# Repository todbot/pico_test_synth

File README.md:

# pico_test_synth

A simple 
[Raspberry Pi Pico RP2040 or Pico 2 RP2350](https://www.raspberrypi.com/documentation/microcontrollers/raspberry-pi-pico.html)-based
synth to experiment with [`synthio`](https://github.com/todbot/circuitpython-synthio-tricks) and [Mozzi](https://github.com/sensorium/Mozzi).

### pico_test_synth2

### pico_test_synth, the original

<h3>video demo</h3>

** **[Available on Tindie](https://www.tindie.com/products/todbot/pico_test_synth/)** **

### Features

* [PCM5102 I2S DAC](https://todbot.com/blog/2023/05/16/cheap-stereo-line-out-i2s-dac-for-circuitpython-arduino-synths/) footprint for high-quality stereo audio out
* Optoisolated MIDI Input via [MIDI TRS-A 3.5mm jack](https://www.perfectcircuit.com/make-noise-0-coast-midi-cable.html)
* MIDI output via MIDI TRS-A 3.5mm jack
* Two pots for controlling parameters
* One switch for controlling parameters
* 16 capsense touch buttons for synth triggering
* USB MIDI in/out of course too
* **(NOTE: the pico_test_synth1 PCB will NOT work with the Pico2, since its RP2350 chip has a hardware error)**

#### pico_test_synth2 vs pico_test_synth

- Both use the same components
- Both run the same code 
- Both fit in the same enclosure
- `pico_test_synth2` drawn in Kicad; `pico_test_synth` drawn in Eagle
- `pico_test_synth2` has square buttons; `pico_test_synth` has round buttons
- `pico_test_synth2` can work with Pico 2 and Pico 
- `pico_test_synth` can only work with Pico1

### Software

Programs written for [`qtpy_synth`](https://github.com/todbot/qtpy_synth/)
will work with this board too with minimal changes.

Some programs written specifically for this board:

* [TBish](https://github.com/todbot/pico_test_synth/tree/main/circuitpython/tbish/) - a TB303-like synth demo ([video demo](https://www.youtube.com/watch?v=1AflpXbEIno))
* [monosynth1](https://github.com/todbot/pico_test_synth/tree/main/arduino/monosynth1) - a full Moog-like monosynth written in Arduino & Mozzi 
* [hwtest](https://github.com/todbot/pico_test_synth/tree/main/circuitpython/hwtest/code.py) - test out the hardware with a simple synth ([video demo](https://www.youtube.com/watch?v=9U2Dn7ckdbs))
* [wavesynth](https://github.com/todbot/pico_test_synth/tree/main/circuitpython/wavesynth/) - port of wavesynth for qtpy_synth board with some improvements

#### See also:
- [CircuitPython Synthio Tricks](https://github.com/todbot/circuitpython-synthio-tricks)
  - Contains [many other synthio examples](https://github.com/todbot/circuitpython-synthio-tricks/tree/main/examples) that can work with this synth with minimal changes
- [Synthio Tutorial](https://todbot.github.io/CircuitPython_Synthio_Tutorial/) 
  - a getting-started guide for `synthio` ending with some full synthesiser voices 

### Enclosure

As seen in the photos, there is a simple [3d-printable enclosure available on Printables](https://www.printables.com/model/784414-case-for-pico_test_synth-circuitpython-synthesizer). 
It's fast to print and you can snap the PCB in to quickly get started,
or use M2.5 screws and nuts to secure the PCB more permanently.

### Pins used

The board uses all of the Raspberry Pi Pico pins:

* `board.GP28` - middle button
* `board.GP27` - right knob
* `board.GP26` - left knob
* `board.GP22` - I2S data
* `board.GP21` - I2S LR  clock
* `board.GP20` - I2S bit clock
* `board.GP19` - I2C SCL for OLED display
* `board.GP18` - I2C SDA for OLED display
* `board.GP17` - TRS UART MIDI in
* `board.GP16` - TRS UART MIDI out
* `board.GP15`..`board.GP0` -- touch pads 1-16

For more details see [`hwtest/code.py`](https://github.com/todbot/pico_test_synth/tree/main/circuitpython/hwtest/code.py).

### Schematics

#### pico_test_synth2 ####

#### pico_test_synth, original ####

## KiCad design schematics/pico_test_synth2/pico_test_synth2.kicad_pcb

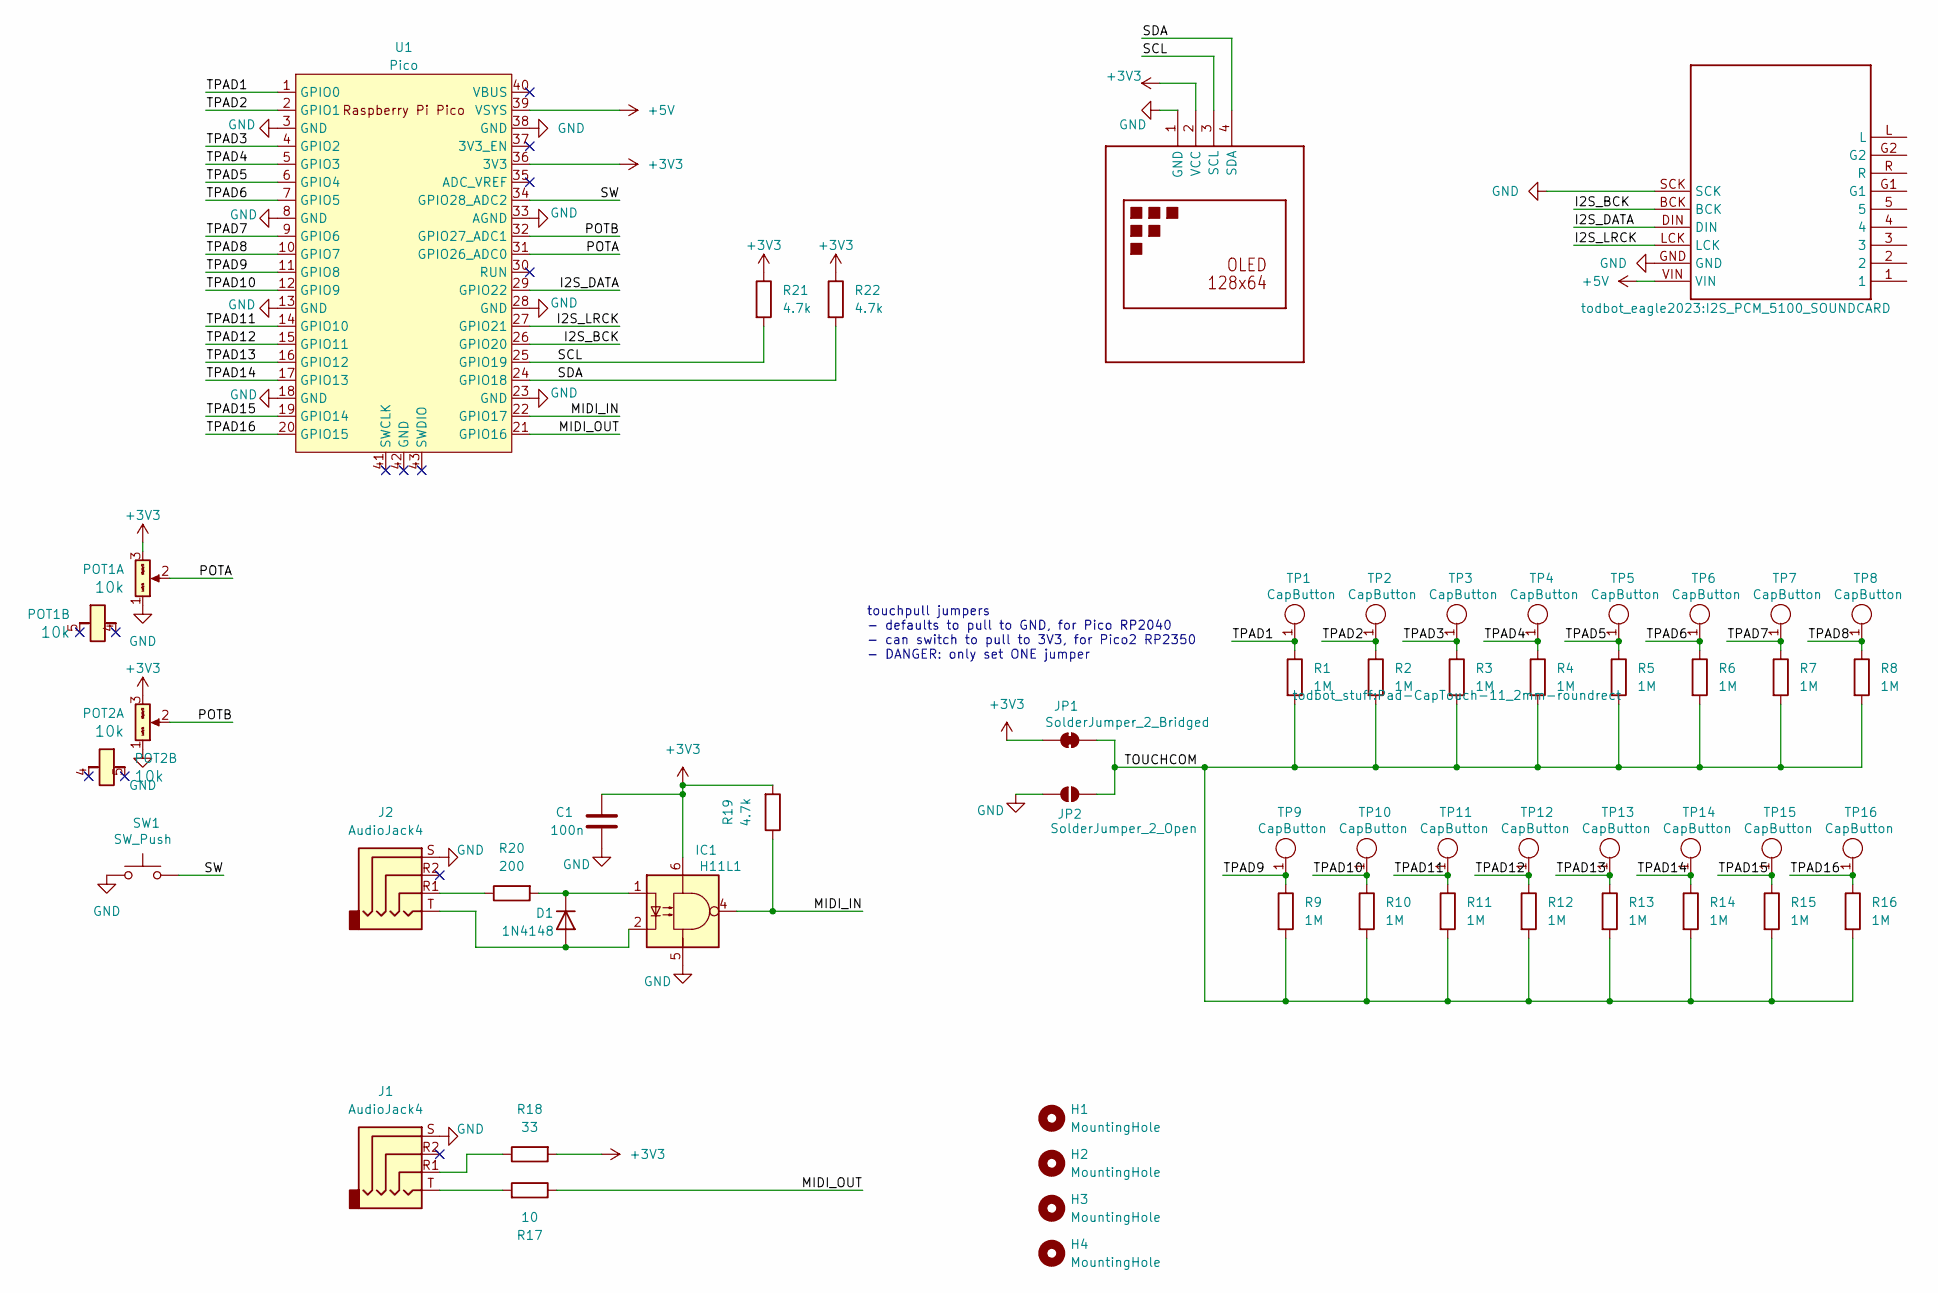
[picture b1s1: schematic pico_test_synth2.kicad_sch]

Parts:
C1: 100n; C_0603_1608Metric
D1: 1N4148; D_SOD-123
DISP1: OLED-TH_over_L27.8-W27.2-P2.54_C9900033791
H1, H2, H3, H4: MountingHole; MountingHole_2.7mm_M2.5
IC1: H11L1; SMD-6_L7.3-W6.5-P2.54-LS10.2-BL; LCSC C78589
J1, J2: AudioJack4; Jack_3.5mm_PJ320D_Horizontal; LCSC C431535
JP1: SolderJumper_2_Bridged; SolderJumper-2_P1.3mm_Bridged_RoundedPad1.0x1.5mm
JP2: SolderJumper_2_Open; SolderJumper-2_P1.3mm_Open_RoundedPad1.0x1.5mm
MODULE1: I2S_PCM_5100_SOUNDCARD
POT1, POT2: 9mm_NoDet_10k_DShaft; Pot_9mm_DShaft; Part Number RV09BCF-40-25F-B10K-007
R1, R2, R3, R4, R5, R6, R7, R8, R9, R10, R11, R12, R13, R14, R15, R16: 1M; R_0603_1608Metric
R17: 10; R_0603_1608Metric
R18: 33; R_0603_1608Metric
R19, R21, R22: 4.7k; R_0603_1608Metric
R20: 200; R_0603_1608Metric
SW1: SW_Push; SW_PUSH_6mm_H4.3mm
TP1, TP2, TP3, TP4, TP5, TP6, TP7, TP8, TP9, TP10, TP11, TP12, TP13, TP14, TP15, TP16: CapButton; Pad-CapTouch-11_2mm-roundrect
U1: Pico; RPi_Pico_SMD_TH

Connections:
+3V3: C1.1, DISP1.2 (VCC), IC1.6, JP1.1 (A), POT1.3 (Right), POT2.3 (Right), R18.2, R19.2, R21.1, R22.1, U1.36 (3V3)
+5V: MODULE1.VIN, U1.39 (VSYS)
/I2S_BCK: MODULE1.BCK, U1.26 (GPIO20)
/I2S_DATA: MODULE1.DIN, U1.29 (GPIO22)
/I2S_LRCK: MODULE1.LCK, U1.27 (GPIO21)
/MIDI_IN: IC1.4, R19.1, U1.22 (GPIO17)
/MIDI_OUT: R17.1, U1.21 (GPIO16)
/POTA: POT1.2 (Center), U1.31 (GPIO26_ADC0)
/POTB: POT2.2 (Center), U1.32 (GPIO27_ADC1)
/SCL: DISP1.3 (SCL), R21.2, U1.25 (GPIO19)
/SDA: DISP1.4 (SDA), R22.2, U1.24 (GPIO18)
/SW: SW1.1, U1.34 (GPIO28_ADC2)
/TOUCHCOM: JP1.2 (B), JP2.2 (B), R1.2, R2.2, R3.2, R4.2, R5.2, R6.2, R7.2, R8.2, R9.2, R10.2, R11.2, R12.2, R13.2, R14.2, R15.2, R16.2
/TPAD1: R1.1, TP1.1 (A), U1.1 (GPIO0)
/TPAD2: R2.1, TP2.1 (A), U1.2 (GPIO1)
/TPAD3: R3.1, TP3.1 (A), U1.4 (GPIO2)
/TPAD4: R4.1, TP4.1 (A), U1.5 (GPIO3)
/TPAD5: R5.1, TP5.1 (A), U1.6 (GPIO4)
/TPAD6: R6.1, TP6.1 (A), U1.7 (GPIO5)
/TPAD7: R7.1, TP7.1 (A), U1.9 (GPIO6)
/TPAD8: R8.1, TP8.1 (A), U1.10 (GPIO7)
/TPAD9: R9.1, TP9.1 (A), U1.11 (GPIO8)
/TPAD10: R10.1, TP10.1 (A), U1.12 (GPIO9)
/TPAD11: R11.1, TP11.1 (A), U1.14 (GPIO10)
/TPAD12: R12.1, TP12.1 (A), U1.15 (GPIO11)
/TPAD13: R13.1, TP13.1 (A), U1.16 (GPIO12)
/TPAD14: R14.1, TP14.1 (A), U1.17 (GPIO13)
/TPAD15: R15.1, TP15.1 (A), U1.19 (GPIO14)
/TPAD16: R16.1, TP16.1 (A), U1.20 (GPIO15)
GND: C1.2, DISP1.1 (GND), IC1.5, J1.S, J2.S, JP2.1 (A), MODULE1.GND, MODULE1.SCK, POT1.1 (Left), POT2.1 (Left), SW1.2, U1.3 (GND), U1.8 (GND), U1.13 (GND), U1.18 (GND), U1.23 (GND), U1.28 (GND), U1.33 (AGND), U1.38 (GND)
unnamed: D1.2 (A), IC1.2, J2.T
unnamed: D1.1 (K), IC1.1, R20.2
unnamed: J1.R1, R18.1
unnamed: J1.T, R17.2
unnamed: J2.R1, R20.1

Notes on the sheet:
touchpull jumpers - defaults to pull to GND, for Pico RP2040 - can switch to pull to 3V3, for Pico2 RP2350 - DANGER: only set ONE jumper

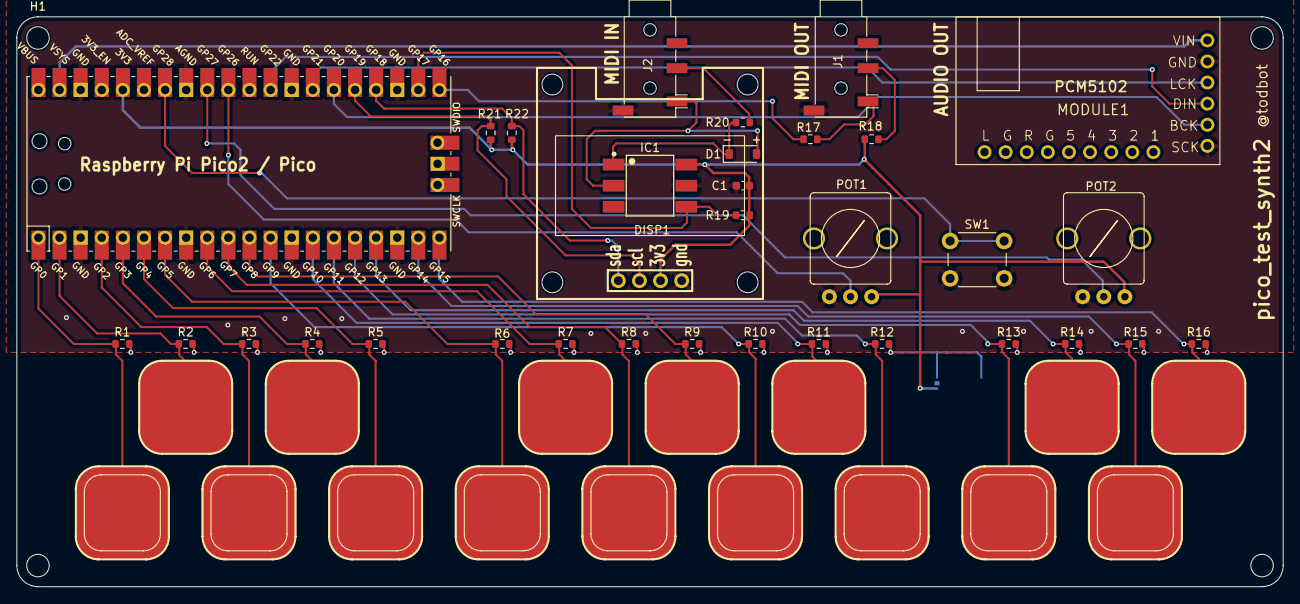
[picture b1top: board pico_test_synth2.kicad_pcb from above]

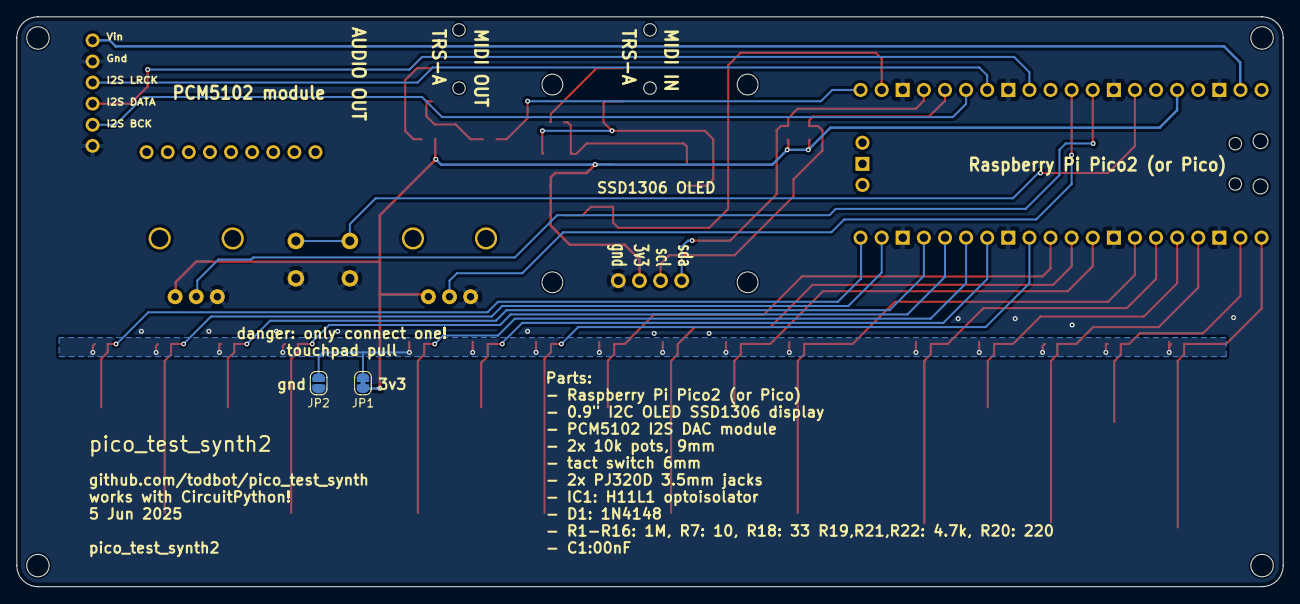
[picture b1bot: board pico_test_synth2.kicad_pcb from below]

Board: 2 copper layers, 152.4 x 68.6 mm, 55 parts (2 on the bottom side), 35 nets.

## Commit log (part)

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2023-08-08 first
2023-08-18 fix up pin usage typos, addresses issue #1
2023-11-22 add synth w/ basic hardware abstraction
2023-11-22 typo fix
2023-11-23 synth1
2024-02-16 clean up hwtest, add rudimentary MIDI receive
2024-02-16 cleanup hwtest a little
2024-02-16 first cut at port of wavesynth from qtpy_synth
2024-02-16 cleanup wavesynth app
2024-02-17 add octave and volume to synthio_instrument patches, expose those params in wavesynth, misc cleanups and fixes. still hate pickup mode
2024-02-17 mention wavesynth in readme
2024-02-17 wavesynth install notes
2024-02-26 finally checking in the restructuring
2024-02-27 add case link to README
2024-02-27 fix wavesynth bugs
2024-02-28 fix more new wavesynth bugs
2024-02-28 wavesynth fixup
2024-02-29 more wavesynth fixes
2024-02-29 wavesynth back to async
2024-03-01 wavesynth filter env works more like it should now
2024-03-01 add some docs
2024-03-02 progress on patch save/load
2024-03-02 wavesynth: patch save/load sorta works, added patch name to display, reworked wave_select logic, added noise wave_select
2024-03-03 wavesynth gauges now redraw on patch selection
2024-03-03 wavesynth twiddling
2024-03-03 wavesynth add splashscreen
2024-03-03 wavesynth instrument.py cleanup
2024-03-03 small hwtest amp env change
2024-03-04 make all waves be half-amplitude (16833) for better multi-voice summing, split out load/save UI actions a little
2024-03-04 wavesynth: add basic velocity sensitivity
2024-03-04 wavesynth: need boot.py to save patches
2024-03-04 fix exec bit on patch_saver.py
2024-03-05 wavesynth: cleanup and added start of demo patch bank
2024-03-28 fix video demo link in readme
2024-07-04 finally getting some arduino examples
2024-07-06 working on arduino gui
2024-07-18 small updates
2024-07-28 add touch keys to monosynth1
2024-07-28 monosynth1: add serial midi in, add start of display
2025-02-15 route +5V to PCM5102 module instead of +3V3, fixes #2
2025-04-15 redraw board in kicad, add ability for using pico2 rp2350
2025-04-16 fixes
2025-04-18 pcb2 cleanup before production
2025-04-18 move pico_test_synth1 sch
2025-04-25 finally check in captouch-only hwtest
2025-04-28 update hwtest for modern circuitpython
2025-05-03 fix up hwtest/code.py a little
2025-05-05 pico_test_synth2 updates
2025-05-15 add pico_test_synth2 to readme
2025-05-15 adj img widths
2025-05-15 add pico_test_synth2 vs original differences
2025-05-25 finally checking in TB-like synth
2025-05-25 finally checked in
2025-05-26 tbish now has touchpad control
2025-05-26 tbish tuning
2025-05-26 tbish slide sorta working
2025-05-27 tbish: misc fixes, added delay (but off)
2025-05-27 tbish envmod and decay work a bit more like 303 now
2025-05-28 tbish: pulled out simple step sequencer to its own class, modeled after synth_tools.step_sequencer
2025-05-29 hooked up delay to knobs, added first cut at save/load of ParamSets
2025-05-29 added wavetype to UI, changed around some other UI, restored drive_mix
2025-05-31 tbish: wired up accent param better, tweaked distortion, added saw2 wave
2025-06-01 tbish: better accent, step display
2025-06-03 add quick tbish readme
2025-06-05 pico_test_synth2 5Jun2025 production run
2025-06-09 fix spdx on .py
2025-06-09 clarify pico2 in readme
2025-06-09 update demos in readme
2025-06-09 update links in readme
2025-11-28 update hwtest/code.py to work with pico_test_synth2 board
2025-11-29 cleanup hwtest code
2025-12-02 fix synth1 for cirpy 10 and pico_test_synth2
2025-12-02 add filter type selection to synth1
2025-12-03 make synth1 dual-voice with detune
2025-12-04 synth1: add simple filter envelope
2025-12-05 synth1 now has per-note filter env with adjustable filter env time using exp filter instead of linear
2025-12-05 synth1: add osc and detune
2025-12-05 synth1: add proper midi input
2025-12-07 cleanup synth1
2025-12-08 synth1: rename pico_test_synth.py to pico_test_synth_hardware.py
2025-12-08 wavesynth1 fixes
2025-12-08 update gitignore
2025-12-08 change synth_tools/instrument to change filter type on keypress
2026-01-14 add video demo link
